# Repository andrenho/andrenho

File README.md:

Welcome!

<!--
**andrenho/andrenho** is a ✨ _special_ ✨ repository because its `README.md` (this file) appears on your GitHub profile.

Here are some ideas to get you started:

- 🔭 I’m currently working on ...
- 🌱 I’m currently learning ...
- 👯 I’m looking to collaborate on ...
- 🤔 I’m looking for help with ...
- 💬 Ask me about ...
- 📫 How to reach me: ...
- 😄 Pronouns: ...
- ⚡ Fun fact: ...
-->

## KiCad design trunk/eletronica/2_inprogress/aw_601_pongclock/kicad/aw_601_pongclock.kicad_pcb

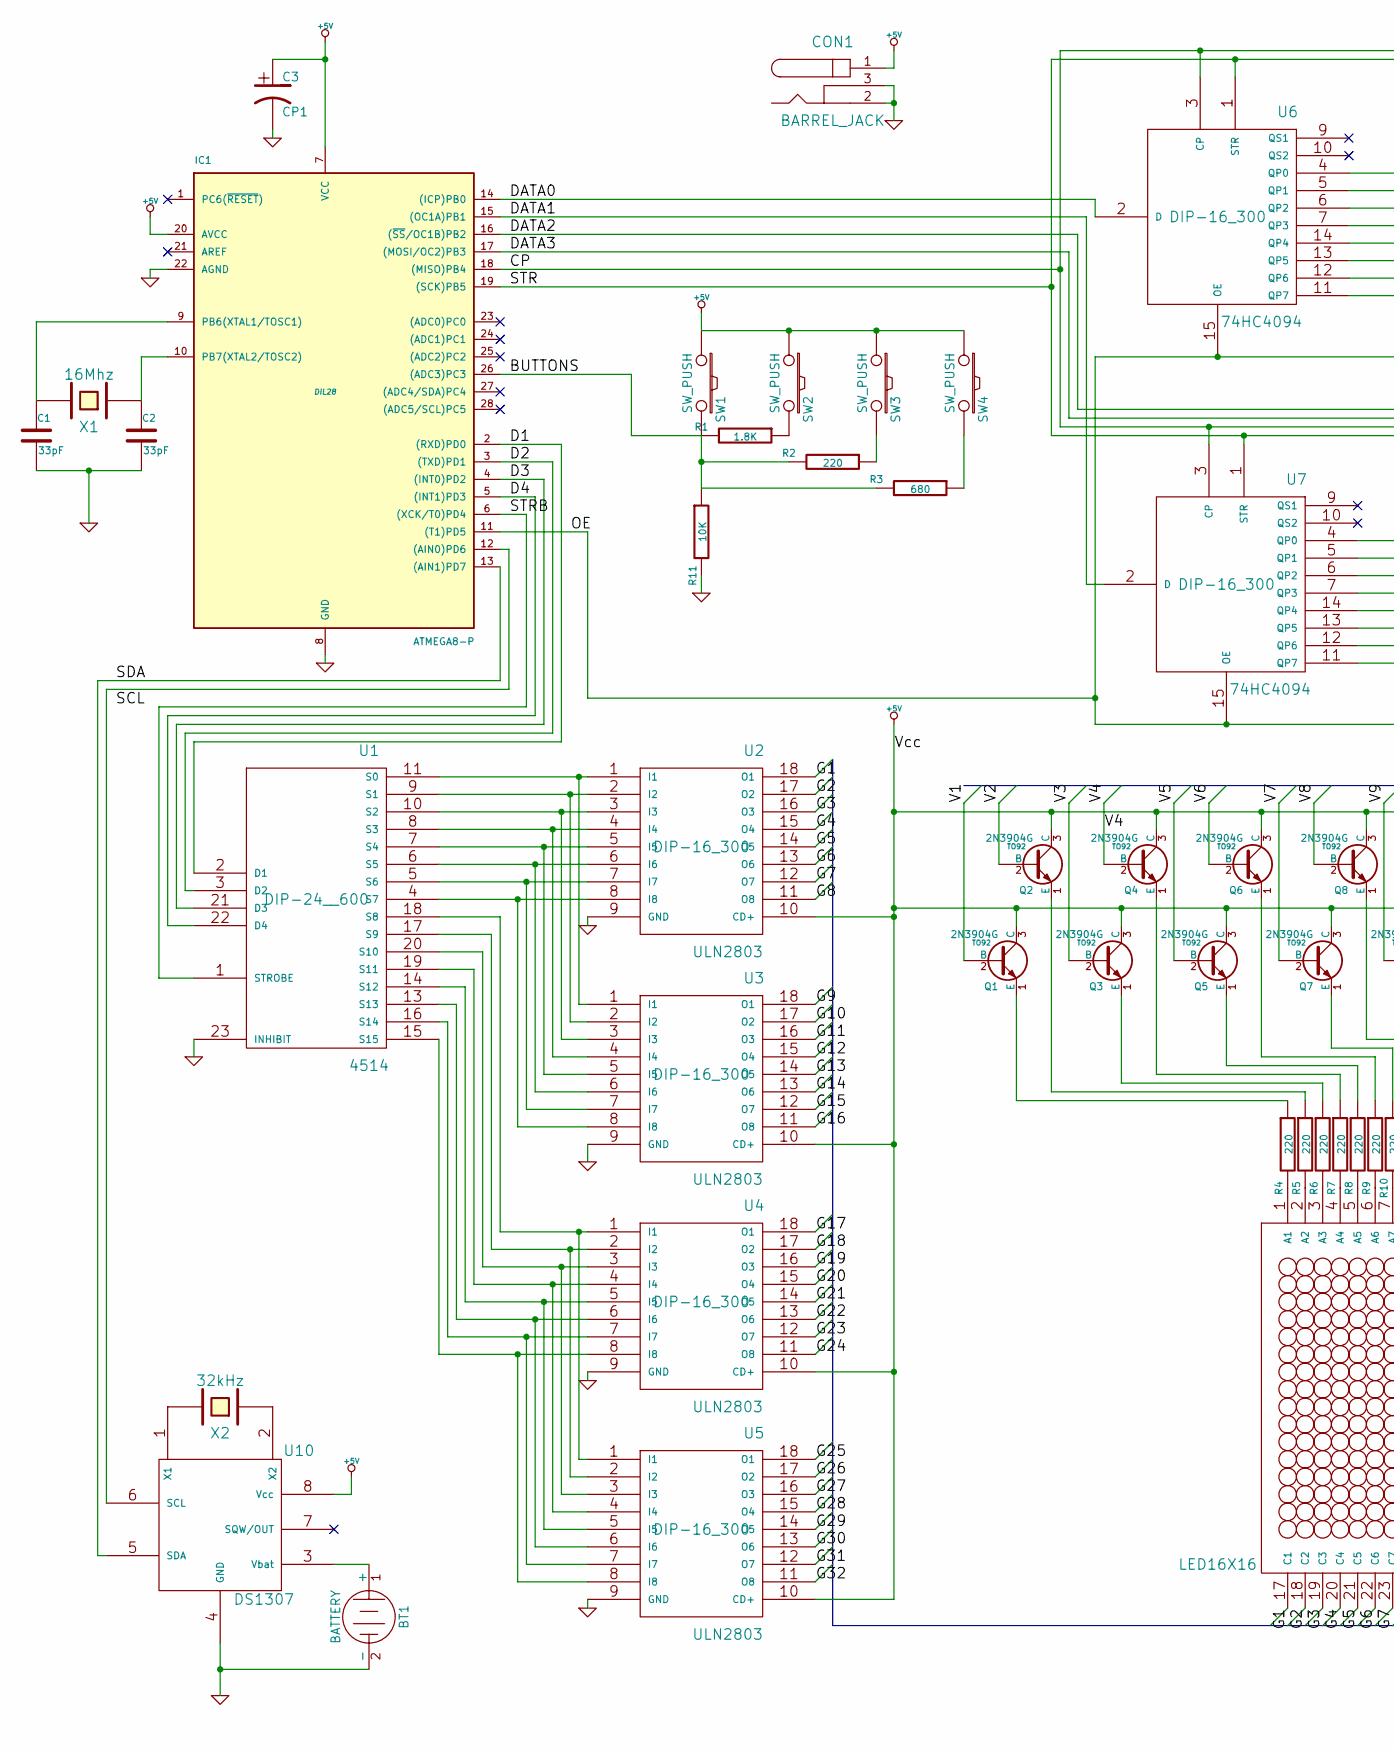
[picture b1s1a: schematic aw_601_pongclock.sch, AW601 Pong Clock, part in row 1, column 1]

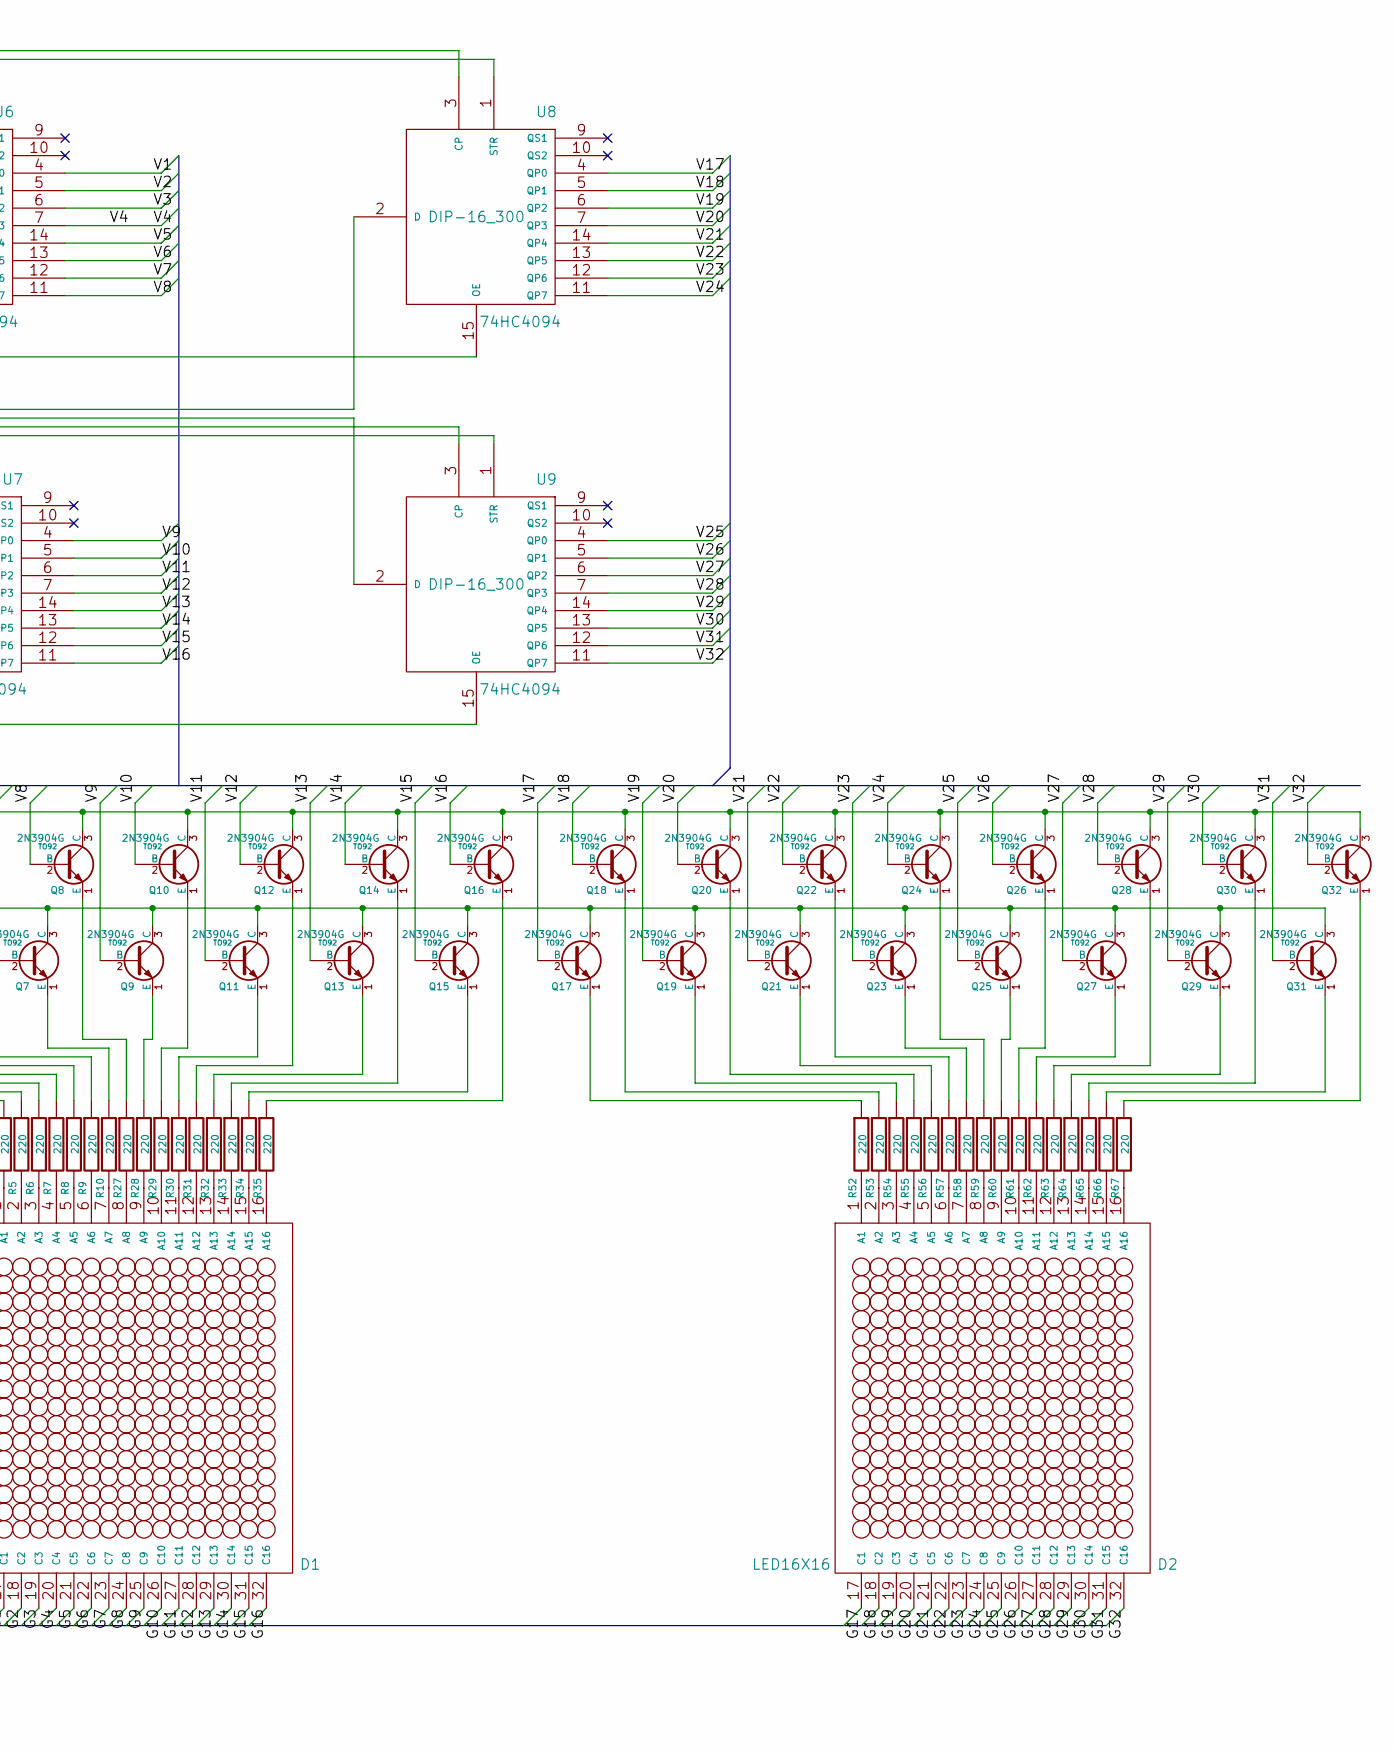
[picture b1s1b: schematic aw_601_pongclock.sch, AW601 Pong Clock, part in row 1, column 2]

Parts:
BT1: BATTERY
C1, C2: 33pF
C3: CP1
CON1: BARREL_JACK
D1, D2: LED16X16
IC1: ATMEGA8-P; DIL28
Q1, Q2, Q3, Q4, Q5, Q6, Q7, Q8, Q9, Q10, Q11, Q12, Q13, Q14, Q15, Q16, Q17, Q18, Q19, Q20, Q21, Q22, Q23, Q24, Q25, Q26, Q27, Q28, Q29, Q30, Q31, Q32: 2N3904G; TO92
R1: 1.8K
R2, R4, R5, R6, R7, R8, R9, R10, R27, R28, R29, R30, R31, R32, R33, R34, R35, R52, R53, R54, R55, R56, R57, R58, R59, R60, R61, R62, R63, R64, R65, R66, R67: 220
R3: 680
R11: 10K
SW1, SW2, SW3, SW4: SW_PUSH
U1: 4514; DIP-24__600
U2, U3, U4, U5: ULN2803; DIP-16_300
U6, U7, U8, U9: 74HC4094; DIP-16_300
U10: DS1307
X1: 16Mhz
X2: 32kHz

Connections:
+5V: C3.1, CON1.1, IC1.7 (VCC), IC1.20 (AVCC), Q1.3 (C), Q2.3 (C), Q3.3 (C), Q4.3 (C), Q5.3 (C), Q6.3 (C), Q7.3 (C), Q8.3 (C), Q9.3 (C), Q10.3 (C), Q11.3 (C), Q12.3 (C), Q13.3 (C), Q14.3 (C), Q15.3 (C), Q16.3 (C), Q17.3 (C), Q18.3 (C), Q19.3 (C), Q20.3 (C), Q21.3 (C), Q22.3 (C), Q23.3 (C), Q24.3 (C), Q25.3 (C), Q26.3 (C), Q27.3 (C), Q28.3 (C), Q29.3 (C), Q30.3 (C), Q31.3 (C), Q32.3 (C), SW1.1, SW2.1, SW3.1, SW4.1, U1.24 (Vcc), U2.10 (CD+), U3.10 (CD+), U4.10 (CD+), U5.10 (CD+), U6.16 (Vcc), U7.16 (Vcc), U8.16 (Vcc), U9.16 (Vcc), U10.8 (Vcc); also elsewhere on the board
/BAT+: BT1.1 (+), U10.3 (Vbat)
/BUTTONS: IC1.26 ((ADC3)PC3), R1.2, R2.2, R3.2, R11.1, SW1.2
/CP: IC1.18 ((MISO)PB4), U6.3 (CP), U7.3 (CP), U8.3 (CP), U9.3 (CP)
/D1: IC1.2 ((RXD)PD0), U1.2 (D1)
/D2: IC1.3 ((TXD)PD1), U1.3 (D2)
/D3: IC1.4 ((INT0)PD2), U1.21 (D3)
/D4: IC1.5 ((INT1)PD3), U1.22 (D4)
/DATA0: IC1.14 ((ICP)PB0), U6.2 (D)
/DATA1: IC1.15 ((OC1A)PB1), U7.2 (D)
/DATA2: IC1.16 ((~SS~/OC1B)PB2), U8.2 (D)
/DATA3: IC1.17 ((MOSI/OC2)PB3), U9.2 (D)
/G1: D1.17 (C1), U2.18 (O1)
/G2: D1.18 (C2), U2.17 (O2)
/G3: D1.19 (C3), U2.16 (O3)
/G4: D1.20 (C4), U2.15 (O4)
/G5: D1.21 (C5), U2.14 (O5)
/G6: D1.22 (C6), U2.13 (O6)
/G7: D1.23 (C7), U2.12 (O7)
/G8: D1.24 (C8), U2.11 (O8)
/G9: D1.25 (C9), U3.18 (O1)
/G10: D1.26 (C10), U3.17 (O2)
/G11: D1.27 (C11), U3.16 (O3)
/G12: D1.28 (C12), U3.15 (O4)
/G13: D1.29 (C13), U3.14 (O5)
/G14: D1.30 (C14), U3.13 (O6)
/G15: D1.31 (C15), U3.12 (O7)
/G16: D1.32 (C16), U3.11 (O8)
/G17: D2.17 (C1), U4.18 (O1)
/G18: D2.18 (C2), U4.17 (O2)
/G19: D2.19 (C3), U4.16 (O3)
/G20: D2.20 (C4), U4.15 (O4)
/G21: D2.21 (C5), U4.14 (O5)
/G22: D2.22 (C6), U4.13 (O6)
/G23: D2.23 (C7), U4.12 (O7)
/G24: D2.24 (C8), U4.11 (O8)
/G25: D2.25 (C9), U5.18 (O1)
/G26: D2.26 (C10), U5.17 (O2)
/G27: D2.27 (C11), U5.16 (O3)
/G28: D2.28 (C12), U5.15 (O4)
/G29: D2.29 (C13), U5.14 (O5)
/G30: D2.30 (C14), U5.13 (O6)
/G31: D2.31 (C15), U5.12 (O7)
/G32: D2.32 (C16), U5.11 (O8)
/OE: IC1.11 ((T1)PD5), U6.15 (OE), U7.15 (OE), U8.15 (OE), U9.15 (OE)
/SCL: IC1.12 ((AIN0)PD6), U10.6 (SCL); also elsewhere on the board
/SDA: IC1.13 ((AIN1)PD7), U10.5 (SDA); also elsewhere on the board
/STR: IC1.19 ((SCK)PB5), U6.1 (STR), U7.1 (STR), U8.1 (STR), U9.1 (STR)
/STRB: IC1.6 ((XCK/T0)PD4), U1.1 (STROBE)
/V1: Q1.2 (B), U6.4 (QP0)
/V2: Q2.2 (B), U6.5 (QP1)
/V3: Q3.2 (B), U6.6 (QP2)
/V4: Q4.2 (B), U6.7 (QP3)
/V5: Q5.2 (B), U6.14 (QP4)
/V6: Q6.2 (B), U6.13 (QP5)
/V7: Q7.2 (B), U6.12 (QP6)
/V8: Q8.2 (B), U6.11 (QP7)
/V9: Q9.2 (B), U7.4 (QP0)
/V10: Q10.2 (B), U7.5 (QP1)
/V11: Q11.2 (B), U7.6 (QP2)
/V12: Q12.2 (B), U7.7 (QP3)
/V13: Q13.2 (B), U7.14 (QP4)
/V14: Q14.2 (B), U7.13 (QP5)
/V15: Q15.2 (B), U7.12 (QP6)
/V16: Q16.2 (B), U7.11 (QP7)
/V17: Q17.2 (B), U8.4 (QP0)
/V18: Q18.2 (B), U8.5 (QP1)
/V19: Q19.2 (B), U8.6 (QP2)
/V20: Q20.2 (B), U8.7 (QP3)
/V21: Q21.2 (B), U8.14 (QP4)
/V22: Q22.2 (B), U8.13 (QP5)
/V23: Q23.2 (B), U8.12 (QP6)
/V24: Q24.2 (B), U8.11 (QP7)
/V25: Q25.2 (B), U9.4 (QP0)
/V26: Q26.2 (B), U9.5 (QP1)
/V27: Q27.2 (B), U9.6 (QP2)
/V28: Q28.2 (B), U9.7 (QP3)
/V29: Q29.2 (B), U9.14 (QP4)
/V30: Q30.2 (B), U9.13 (QP5)
/V31: Q31.2 (B), U9.12 (QP6)
/V32: Q32.2 (B), U9.11 (QP7)
GND: BT1.2 (-), C1.2, C2.2, C3.2, CON1.2, CON1.3, IC1.8 (GND), IC1.22 (AGND), R11.2, U1.12 (GND), U1.23 (INHIBIT), U2.9 (GND), U3.9 (GND), U4.9 (GND), U5.9 (GND), U6.8 (GND), U7.8 (GND), U8.8 (GND), U9.8 (GND), U10.4 (GND)
unnamed: Q1.1 (E), R4.1
unnamed: Q6.1 (E), R9.1
unnamed: Q5.1 (E), R8.1
unnamed: Q4.1 (E), R7.1
unnamed: Q12.1 (E), R31.1
unnamed: Q9.1 (E), R28.1
unnamed: Q10.1 (E), R29.1
unnamed: Q11.1 (E), R30.1
unnamed: Q13.1 (E), R32.1
unnamed: Q14.1 (E), R33.1
unnamed: Q3.1 (E), R6.1
unnamed: Q2.1 (E), R5.1
unnamed: Q7.1 (E), R10.1
unnamed: Q8.1 (E), R27.1
unnamed: Q15.1 (E), R34.1
unnamed: U1.5 (S6), U2.7 (I7), U3.7 (I7)
unnamed: U1.7 (S4), U2.5 (I5), U3.5 (I5)
unnamed: U1.6 (S5), U2.6 (I6), U3.6 (I6)
unnamed: U1.4 (S7), U2.8 (I8), U3.8 (I8)
unnamed: U1.13 (S13), U4.6 (I6), U5.6 (I6)
unnamed: U1.16 (S14), U4.7 (I7), U5.7 (I7)
unnamed: U1.15 (S15), U4.8 (I8), U5.8 (I8)
unnamed: U1.20 (S10), U4.3 (I3), U5.3 (I3)
unnamed: U1.18 (S8), U4.1 (I1), U5.1 (I1)
unnamed: U1.17 (S9), U4.2 (I2), U5.2 (I2)
unnamed: U1.8 (S3), U2.4 (I4), U3.4 (I4)
unnamed: U1.19 (S11), U4.4 (I4), U5.4 (I4)
unnamed: U1.14 (S12), U4.5 (I5), U5.5 (I5)
unnamed: Q24.1 (E), R59.1
unnamed: Q21.1 (E), R56.1
unnamed: Q23.1 (E), R58.1
unnamed: Q25.1 (E), R60.1
unnamed: Q26.1 (E), R61.1
unnamed: Q27.1 (E), R62.1
unnamed: Q16.1 (E), R35.1
unnamed: Q17.1 (E), R52.1
unnamed: Q22.1 (E), R57.1
unnamed: Q20.1 (E), R55.1
unnamed: Q19.1 (E), R54.1
unnamed: Q18.1 (E), R53.1
unnamed: U1.11 (S0), U2.1 (I1), U3.1 (I1)
unnamed: U1.9 (S1), U2.2 (I2), U3.2 (I2)
unnamed: U1.10 (S2), U2.3 (I3), U3.3 (I3)
unnamed: Q30.1 (E), R65.1
unnamed: Q28.1 (E), R63.1
unnamed: Q29.1 (E), R64.1
unnamed: Q31.1 (E), R66.1
unnamed: Q32.1 (E), R67.1
unnamed: R3.1, SW4.2
unnamed: R2.1, SW3.2
unnamed: U10.1 (X1), X2.2
unnamed: U10.2 (X2), X2.1
unnamed: C1.1, IC1.9 (PB6(XTAL1/TOSC1)), X1.2
unnamed: C2.1, IC1.10 (PB7(XTAL2/TOSC2)), X1.1
unnamed: D1.4 (A4), R7.2
unnamed: D1.10 (A10), R29.2
unnamed: D1.9 (A9), R28.2
unnamed: D1.8 (A8), R27.2
unnamed: D1.7 (A7), R10.2
unnamed: D1.6 (A6), R9.2
unnamed: D1.5 (A5), R8.2
unnamed: D1.11 (A11), R30.2
unnamed: D1.3 (A3), R6.2
unnamed: D1.2 (A2), R5.2
unnamed: D1.1 (A1), R4.2
unnamed: D1.14 (A14), R33.2
unnamed: D1.16 (A16), R35.2
unnamed: D1.15 (A15), R34.2
unnamed: D1.13 (A13), R32.2
unnamed: D1.12 (A12), R31.2
unnamed: R1.1, SW2.2
unnamed: D2.16 (A16), R67.2
unnamed: D2.15 (A15), R66.2
unnamed: D2.5 (A5), R56.2
unnamed: D2.4 (A4), R55.2
unnamed: D2.3 (A3), R54.2
unnamed: D2.2 (A2), R53.2
unnamed: D2.1 (A1), R52.2
unnamed: D2.6 (A6), R57.2
unnamed: D2.14 (A14), R65.2
unnamed: D2.13 (A13), R64.2
unnamed: D2.12 (A12), R63.2
unnamed: D2.11 (A11), R62.2
unnamed: D2.10 (A10), R61.2
unnamed: D2.9 (A9), R60.2
unnamed: D2.8 (A8), R59.2
unnamed: D2.7 (A7), R58.2

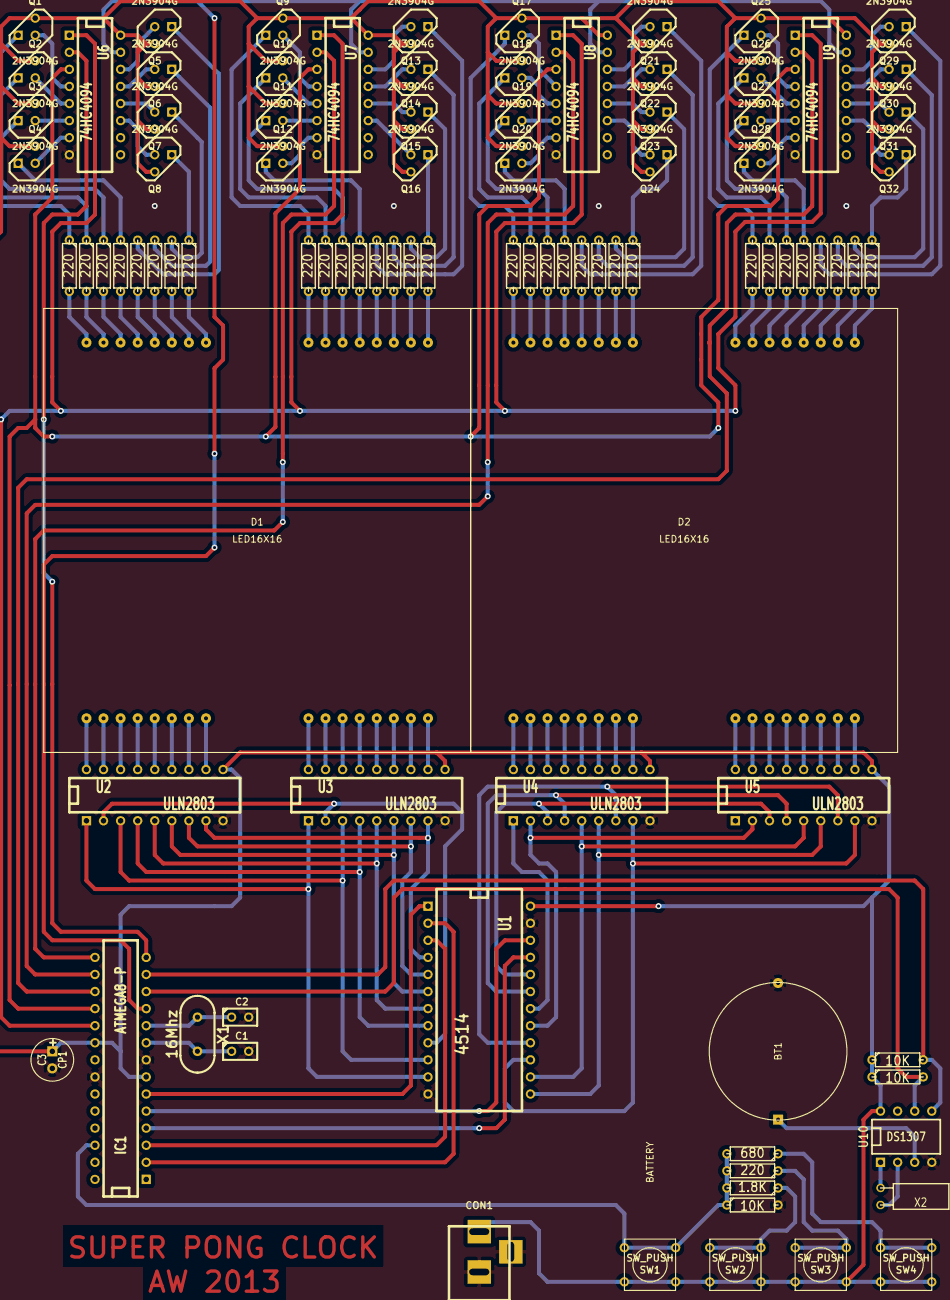
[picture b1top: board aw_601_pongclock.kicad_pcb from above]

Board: 2 copper layers, 94 parts (0 on the bottom side), 169 nets.

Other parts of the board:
R12, R13: 10K; R3

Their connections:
+5V: R12.1, R13.1; also elsewhere on the board
/SCL: R12.2; also elsewhere on the board
/SDA: R13.2; also elsewhere on the board

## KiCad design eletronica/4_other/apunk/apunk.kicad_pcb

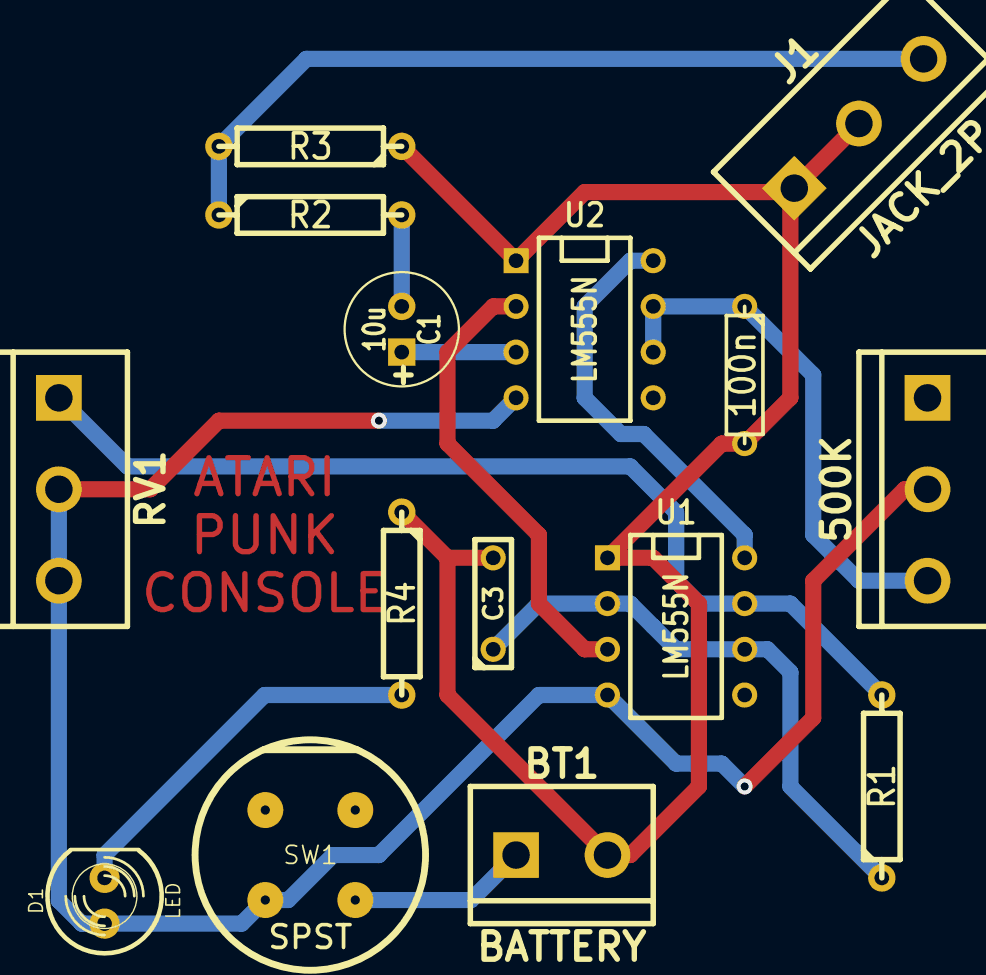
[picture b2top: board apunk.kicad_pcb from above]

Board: 2 copper layers, 15 parts (0 on the bottom side), 12 nets.

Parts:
BT1: BATTERY; bornier2
C1: 10u; C1V7
C3: 10n; C2
C4: 100n; R3
D1: LED; LED-5MM
J1: JACK_2P; bornier3
R1: 1K; R4
R2: 10K; R4
R3: 6K8; R4
R4: 680; R4
RV1, RV2: 500K; bornier3
SW1: SPST; PUSH_BUTT_SHAPE1
U1, U2: LM555N; DIP-8__300

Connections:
+9V: D1.1, RV1.2, RV1.3, RV2.1, RV2.2, SW1.2, U1.4, U2.4
GND: BT1.2, C3.2, C4.2, J1.1, J1.2, R3.1, R4.1, U1.1, U2.1
unnamed: BT1.1, SW1.1
unnamed: C3.1, R1.1, U1.2, U1.6
unnamed: J1.3, R2.1, R3.2
unnamed: D1.2, R4.2
unnamed: C1.1, U2.3
unnamed: U1.3, U2.2
unnamed: R1.2, RV1.1, U1.7
unnamed: C4.1, RV2.3, U2.6, U2.7
unnamed: C1.2, R2.2
VCC: U1.8, U2.8

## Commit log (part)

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2015-03-16 Migrating wiki contents from Google Code
